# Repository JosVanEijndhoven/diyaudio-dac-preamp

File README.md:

# DACXO: Audio DAC and digital pre-amp with low jitter

## Introduction

This [github repository](https://github.com/JosVanEijndhoven/diyaudio-dac-preamp) 
provides all HW and SW sources of my DIY audio DAC design.
The audio 'Digital-to-Analog Conversion' is the heart and main aim of the design.
However, more audio device functionality was built around that:

- Functionality for a digital pre-amp is provided, with input selection
  and volume control. Inputs are optical and coax s/pdif, HDMI-arc, and a network DLNA audio player.
- The control UI (user interface) is created with [esphome](https://esphome.io/).
  Besides the front panel control knob, this also provides remote control from a mobile phone
  and/or integration in [home assistant](https://www.home-assistant.io/) automation environments.
- The core DAC design aims for high-end audio, with a focus on low jitter, not
  aiming to reach low component cost.

The intention of this repository is to show some solutions across a wide range of design choices,
potentially of interest to other DIY audio enthousiasts.
Supporting purely cloning the full hw/sw design is not the intention,
as some design files might be outdated for the various tools and components that were used:
the design start was around 2015. (But its development still continous in 2026...)
This DAC design builds on previous experience: it is already my 5th design.

Only in december 2025 I started to upload my design in github, and thereby make it public visible.
I still have to spend further effort in documenting the design and its choices.

The device name **DACXO** is related to:
- Its good **X**tal **O**scillator and low-jitter clocking.
- Its **X**tra **O**riginal clock synchronization scheme on the s/pdif inputs.
- The now **X** [years](https://en.wikipedia.org/wiki/Roman_numerals) **O**ld circuit design when creating this open-source repository.
- As bonus, the domain name [dacxo](http://www.dacxo.com) was available.

## Contents

This repository contains all hardware and software design aspects:

- The [front control and remote UI software](./esphome-ui/) based on a commercial *esp32-s3* board with display.
- The [digital signal processing board](./dacxo-hw/PCBs/PCB-dacxo/), schematics and PCB design.
- The [logic configuration of the FPGA](./dacxo-hw/FPGA-content/) on that board,
- The [analog output board](./dacxo-hw/PCBs/PCB-opampout/), schematics and PCB design,
- A [Linux kernel audio device driver](./dacxo-sw/RPi-audiodevice/),
  so that the board can also be driven from various applications on a Rapsberry Pi.
- Addition of a Raspberry Pi as [network media player](./dacxo-sw/), relying on above audio device driver.

## Focus on Jitter

The main focus on this design is having good behavior on jitter (that is, achieve very low jitter).
Already for decades now, jitter is known to badly affect the sound quality of digital audio reproduction.
Unfortunately, achieving low jitter makes a device more expensive, and measuring jitter behavior requires expensive specialised equipment.
As result, many digital audio consumer products still show bad jitter behavoir.

The audible effects of jitter in a digital audio player are:

- Weak, uncontrolled, bass
- Unfocussed and unstable stereo imaging
- Unpleasantly sharp (metal-sounding) highs

Because many (cheaper) audio consumer devices behave badly in this respect,
the old vinyl record playing has risen again in popularity.
Luckily, good digital audio players don't show these artifacts,
and can sound really natural and convincing!

Presumably in large part due to jitter effects, this DAC design sounds significantly better than for instance the
[Cambridge Audio EXN100 player](https://www.cambridgeaudio.com/row/en/products/ex/exn100) which I bought early 2025, 
which costs around 2000 US$. (Just in my opinion and some of my audio-loving friends.)

For further background information on jitter in digital audio, you can easily find many sources on internet.

As a final note, jitter artefacts do not only occur in audio DAC (digital-to-analog conversion),
but similarly in analog-to-digital conversion (ADC).
So, a poor-quality studio recording (or home recording)
will introduce jitter artefacts in the digital audio stream.
Once in there, these jitter artefacts cannot be removed anymore:
a bad recording will sound bad forever. 
A good low-jitter player cannot improve a bad recording.
Unfortunately, it seems to me that there are many bad-quality recordings around...

## License
All source and configuration files provided in this repository are provided without any warrenty,
and under copyright and license:

Copyright 2025 Jos van Eijndhoven

[GNU General Public License v3](https://www.gnu.org/licenses/gpl-3.0.nl.html)

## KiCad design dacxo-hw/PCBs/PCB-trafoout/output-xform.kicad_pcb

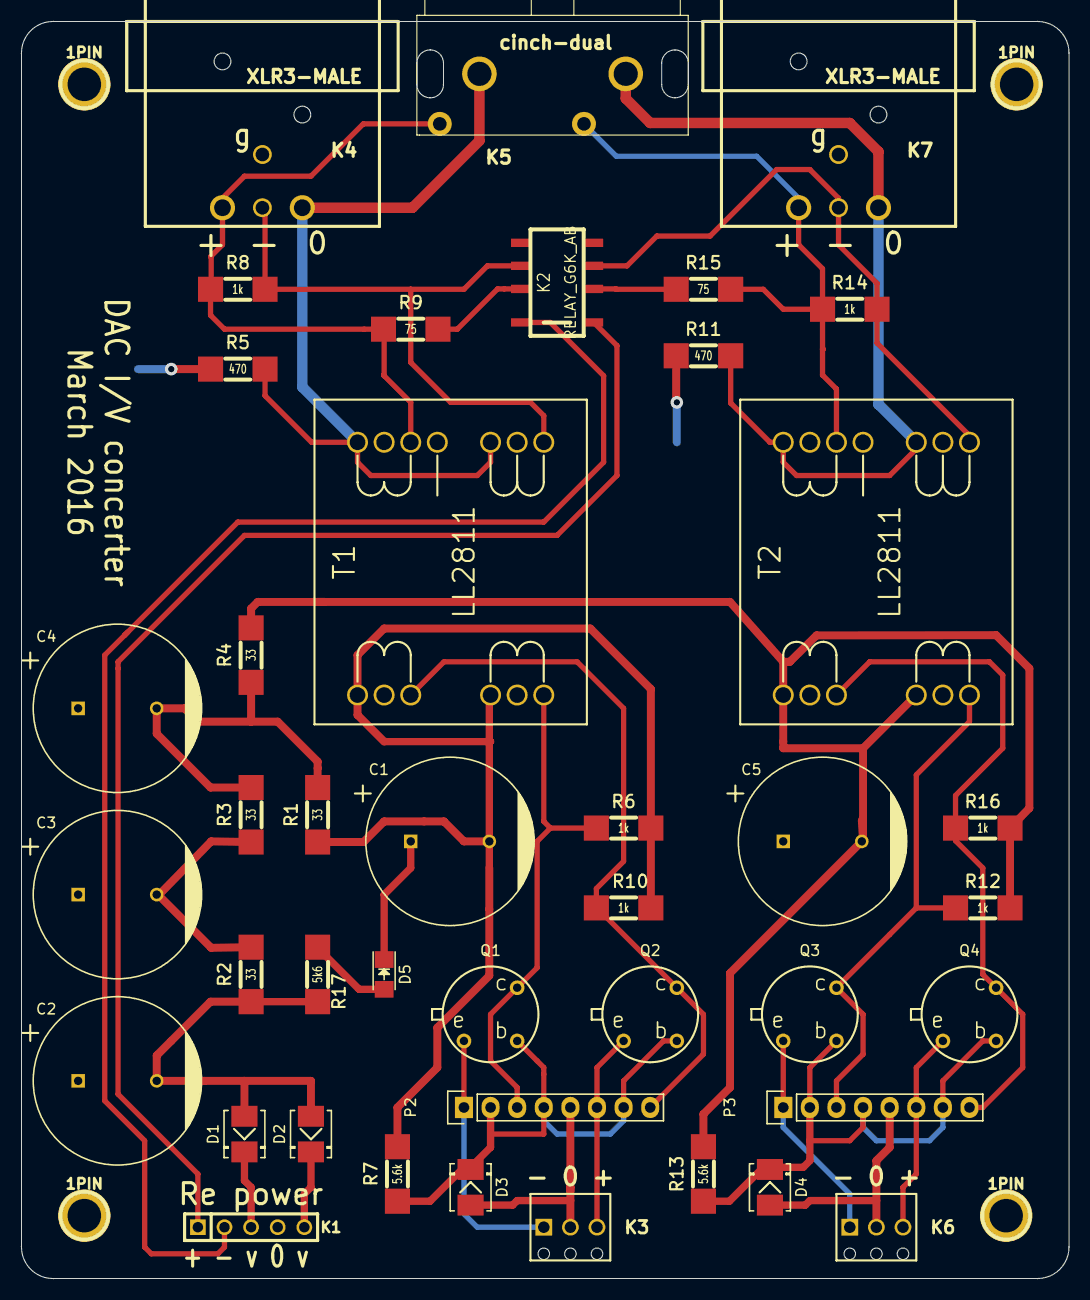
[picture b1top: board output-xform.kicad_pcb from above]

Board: 2 copper layers, 100.0 x 120.0 mm, 46 parts (0 on the bottom side), 29 nets.

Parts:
1PIN, 1PIN#2, 1PIN#3, 1PIN#4: P***; screw-3.2
C1, C2, C3, C4, C5: 4.7mF; C_Radial_D16_L30_P7.5
D1, D2, D3, D4: DIODE; DO-214
D5: LED; LED_1206
K1: CONN_01X05; SIL-5
K2: RELAY_G6K_AB; G6K-2F-Y
K3, K6: CONN_3; SIL-3-screw
K4, K7: XLR3-MALE; NC3MAH
K5: cinch-dual; dualphono-kobiconn
P2, P3: CONN_01X08; Pin_Header_Straight_1x08
Q1, Q2, Q3, Q4: 2N2905A; 2N2905-TO5
R1, R2, R3, R4: 33; MMB0207
R5, R11: 470; MMB0207
R6, R8, R10, R12, R14, R16: 1k; MMB0207
R7, R13: 5.6k; MMB0207
R9, R15: 75; MMB0207
R17: 5k6; MMB0207
T1, T2: LL2811

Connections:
-12VL: C1.2, R1.2, R6.2, R7.2, R10.1, T1.3, T1.8
-12VR: C5.2, R4.2, R12.2, R13.2, R16.1, T2.3, T2.8
/-16V: C2.2, D1.1, D2.1, R2.1, R17.1
/ReN: K1.2, K2.8
/ReP: K1.1, K2.1
/baseL: D3.2, P2.2, P2.4, P2.7, Q1.2, Q2.2, R7.1
/baseR: D4.2, P3.2, P3.4, P3.7, Q3.2, Q4.2, R13.1
/inLneg: K3.1, P2.1, Q1.1
/inLpos: K3.3, P2.6, Q2.1
/inRneg: K6.1, P3.1, Q3.1
/inRpos: K6.3, P3.6, Q4.1
/primLneg: P2.3, Q1.3, R6.1, T1.1
/primLpos: P2.8, Q2.3, R10.2, T1.6
/primRPos: P3.8, Q4.3, R16.2, T2.6
/primRneg: P3.3, Q3.3, R12.1, T2.1
AGND: C1.1, C2.1, C3.1, C4.1, C5.1, D3.1, D4.1, D5.1, K1.4, K3.2, K6.2, P2.5, P3.5, R5.1, R11.1, T1.13, T2.13
unnamed: C3.2, R2.2, R3.1
unnamed: C4.2, R1.1, R3.2, R4.1
unnamed: D1.2, K1.3
unnamed: D2.2, K1.5
unnamed: D5.2, R17.2
unnamed: K2.2, R15.1
unnamed: K2.3, K7.3, R14.1, T2.9
unnamed: K2.6, K4.3, R8.1, T1.9
unnamed: K2.7, R9.1
unnamed: K4.1, K5.3, R5.2, T1.11, T1.16
unnamed: K4.2, K5.2, R8.2, R9.2, T1.14
unnamed: K5.1, K7.2, R14.2, R15.2, T2.14
unnamed: K5.4, K7.1, R11.2, T2.11, T2.16

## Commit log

2025-12-10 Gathered hw and sw files
2025-12-13 extend README text, fpga info
2025-12-29 Update kernel Makefile
2026-01-03 Many fixes in RPi device drivers: now compilable, unuse my old pcm1792a i2c driver
2026-01-03 small Makefile update, enable i2s in config
2026-01-03 jedac5: omit kernel header for pcm179x
2026-01-06 Update description of dig pcb, add patch pictures
2026-01-06 Update description of opamp pcb
2026-01-06 Update description of dig pcb
2026-01-06 Update description of dig pcb with led status
2026-01-06 Update description of dig pcb: add dac solder pic
2026-01-07 update audiodev Makefile
2026-01-09 Update jedac drivers and dts to add gpio pin
2026-01-09 fix overlay for unknown flags
2026-01-09 fix overlay for bcm2710 for pi zero 2w
2026-01-20 Small driver updates, diagnostic prints
2026-01-20 Try to resolve missing call to probe on pcm179x
2026-01-20 reestablish my own pcm1792a driver, due to bug in kernel pcm179x: missing .cache_type in regmap_config
2026-01-20 test different regmap_config cache_type
2026-01-20 fix bug on regmap_config in pcm1792a
2026-01-21 Change 'compatible' driver name from ti to jve
2026-01-22 further change name of compatible driver to jve1792a
2026-01-22 fix 'compatible' name of 1792a, fix 'depmod'
2026-01-22 rename 'pcm1792' to 'jve1792' to avoid ko name conflicts
2026-01-22 fix use of 'of_node_put', fix 'i2c_codec_node'
2026-01-22 fix .name=null when setting node ptr
2026-01-22 Add creating INSTALLDIR to Makefile
2026-01-24 First wave of edits for a modified sw architecture, not yet working
2026-01-25 first prelim version of renewed asoc structuring
2026-01-26 Rename 'jedac5' to 'jedac'
2026-01-26 Fix old leftover in codec
2026-01-26 Cleanup pcm1792 driver and dts reference
2026-01-26 Update dts
2026-01-26 Update bcm: try to avoid crash
2026-01-26 fix 'compatible' names in .c and .dts
2026-01-26 fix i2s reference in .dts
2026-01-26 fix jedac_codec reference?
2026-01-26 fix jedac_bcm register message
2026-01-27 handle i2c bus errs in codec
2026-01-29 Add DAPM power management to take device out of standby mode'
2026-01-29 Makefile skip 'depmod' (should be part of 'modules_install', add 'show_regs'
2026-01-30 Implement 'regmap' feature for both DACs
2026-01-30 Hint the kernel on dependency on regmap
2026-01-30 Fix register init of pcm1792 dacs
2026-01-30 Fix register init of pcm1792 dacs - debug
2026-01-30 Added 'regcache_cache_only', and debug prints
2026-02-05 small fixes in bcm, set 'uisync' gpio
2026-02-05 fix regmap allocation during probe
2026-02-05 Add input select control
2026-02-06 Add 'uisync' gpio pulse to codec
2026-02-06 Simplify asound.conf for now
2026-02-06 Fix power-on event
2026-02-06 Fix gpio pulldown, reduce test logging
2026-02-06 Update dts form campatibility with more RPi models, make uisync pin a parameter, provide a systemd 'jedac.service'
2026-02-06 Update Make target install
2026-02-06 Small comment update in yaml
2026-02-06 Fix default audio for converting of 'S24_3LE' flac output
2026-02-06 Codec guard actual i2c write for samplerate
2026-02-07 cleanup Makefile, initialize devicedriver md
2026-02-07 Move files from jedac_soc_modules one level up
2026-02-07 Updated README, describing the Pi device device driver
2026-02-07 Update pi driver README
2026-02-09 Extend README on dlna player and the device driver
2026-02-12 Create CNAME
2026-02-12 rename 'jedac' to 'dacxo'
2026-03-01 Small update top README
2026-03-01 RPi driver: do not take input sel on power-up
2026-03-13 Remove 'defaults' from regmap, to avoid bad view on content
2026-03-14 Fix 'ui_sync' updates when RPi player present
2026-03-14 Use the 'dacxo' card in Linux NOT as default
2026-04-12 Improve cooperation with external microcontroller
2026-04-12 Fix typo in README
